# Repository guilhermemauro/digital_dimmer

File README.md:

#Welcome to Dimmer Arduino code!

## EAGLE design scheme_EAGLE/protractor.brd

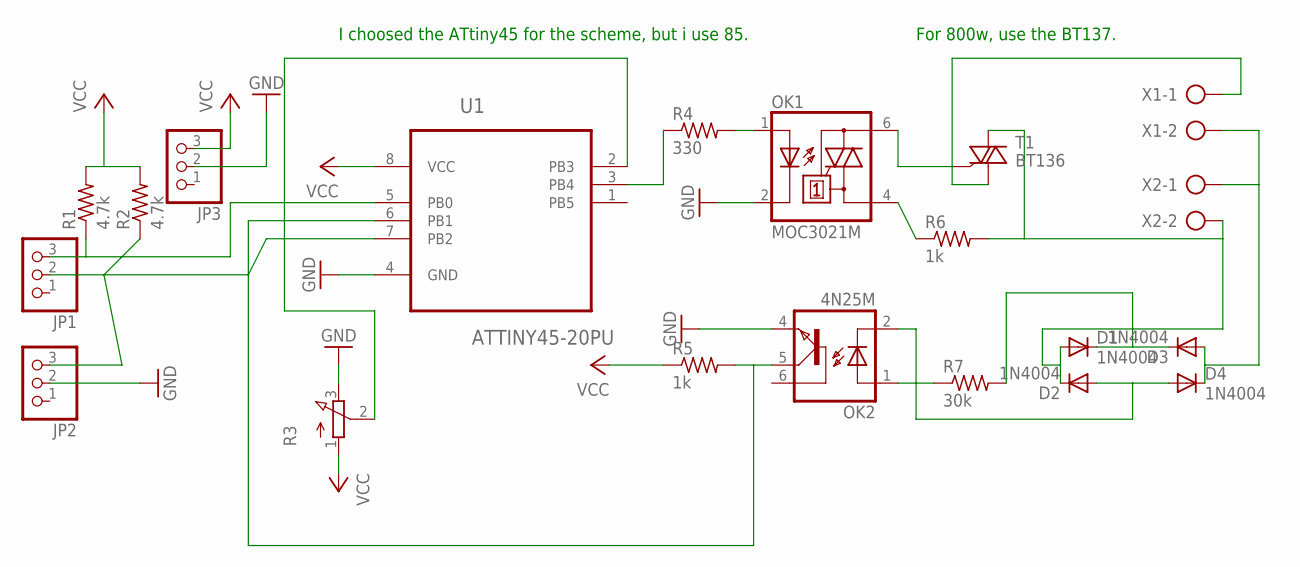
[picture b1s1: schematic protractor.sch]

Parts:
D1, D2, D3, D4: 1N4004; DO41-10
JP1, JP2, JP3: PINHD-1X3; 1X03
OK1: MOC3021M; DIL06
OK2: 4N25M; DIL06
R1, R2: 4.7k; 0207/12
R3: 3RP/1610N
R4: 330; 0207/12
R5, R6: 1k; 0207/12
R7: 30k; 0207/12
T1: BT136; TO220AB
U1: ATTINY45-20PU; DIP254P762X533-8
X1, X2: AK500/2-H

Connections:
GND: JP2.2, JP3.2, OK1.2 (C), OK2.4 (EMI), R3.3 (E), U1.4 (GND); also elsewhere on the board
unnamed: D2.A, D4.A, OK2.2 (C)
unnamed: D1.C, D3.C, R7.2
unnamed: D3.A, D4.C, X1.2, X2.1
unnamed: D1.A, D2.C, R6.2, T1.2 (A2), X2.2
unnamed: OK2.1 (A), R7.1
unnamed: OK1.6 (A2), T1.3 (G)
unnamed: OK1.4 (A1), R6.1
unnamed: T1.1 (A1), X1.1
unnamed 9: R3.2 (S), U1.2 (PB3); also elsewhere on the board
unnamed 10: OK2.5 (COL), R5.2, U1.6 (PB1); also elsewhere on the board
unnamed 11: JP1.3, R1.1, U1.5 (PB0); also elsewhere on the board
unnamed 12: R4.1, U1.3 (PB4); also elsewhere on the board
unnamed: OK1.1 (A), R4.2
unnamed 14: JP1.2, JP2.3, R2.1, U1.7 (PB2); also elsewhere on the board
VCC: JP3.3, R1.2, R2.2, R3.1 (A), R5.1, U1.8 (VCC); also elsewhere on the board

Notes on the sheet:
For 800w, use the BT137.
I choosed the ATtiny45 for the scheme, but i use 85.

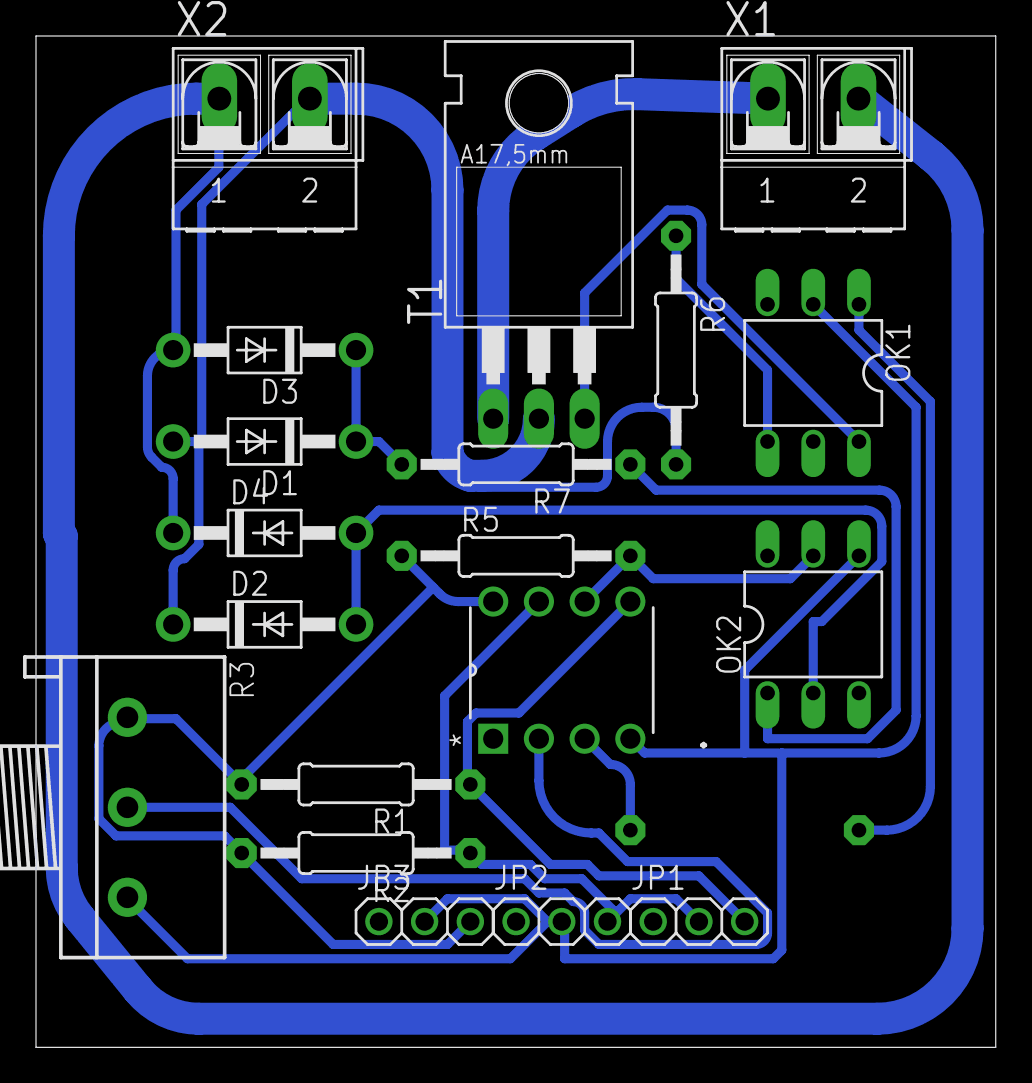
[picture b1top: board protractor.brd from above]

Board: 2 copper layers, 53.3 x 56.2 mm, 20 parts (1 on the bottom side), 16 nets.

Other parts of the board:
.: attiny; DIP254P762X533-8

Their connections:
GND: ..4; also elsewhere on the board
unnamed 9: ..2; also elsewhere on the board
unnamed 10: ..6; also elsewhere on the board
unnamed 11: ..5; also elsewhere on the board
unnamed 12: ..3; also elsewhere on the board
unnamed 14: ..7; also elsewhere on the board
VCC: ..8; also elsewhere on the board

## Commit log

2015-07-11 Maked the Arduino Uno dimmer source.
2015-07-11 Added the README file on project.
2015-07-11 The first phrase add in README
2015-07-11 Maked the file source of Arduino Dimmer.
2015-07-11 The file is trash. No more.
2015-07-11 Added the first part of the source.
2015-07-11 First test with Zerocrossing Detector.
2015-07-11 Zerocrossing works.
2015-07-12 Update to work the dimmer in Arduino Uno.
2015-07-12 Potentiometer added in source. Now its possible controler the dimmer with potentiometer.
2015-07-13 Just a little correction.
2015-07-31 Create the file for scheme in CadSoft Eagle.
2015-07-31 Added the bridge retifier and BT137.
2015-07-31 Components files.
2015-07-31 Schema done, inserted news components.
2015-07-31 Inserted the switch to choose between Arduino Comands and Potentiometer
2015-07-31 I added coments, and pullup for i2c comunication.
2015-07-31 Rename the components
2015-07-31 Created the board file.
2015-07-31 Make the first version of the dimmer board
2015-07-31 Route configured.
2015-07-31 Created new files board.
2015-08-03 The source is portable for Attiny85/45
2015-08-03 A little correction on the function map.
2015-08-04 Change the pins for use on the board scheme.
2016-01-19 Added the i2c suport for ATtiny
2016-02-22 Now, the firmware is works
